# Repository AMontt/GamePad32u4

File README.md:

# GamePad32u4
Basic gamepad using ATMega32u4

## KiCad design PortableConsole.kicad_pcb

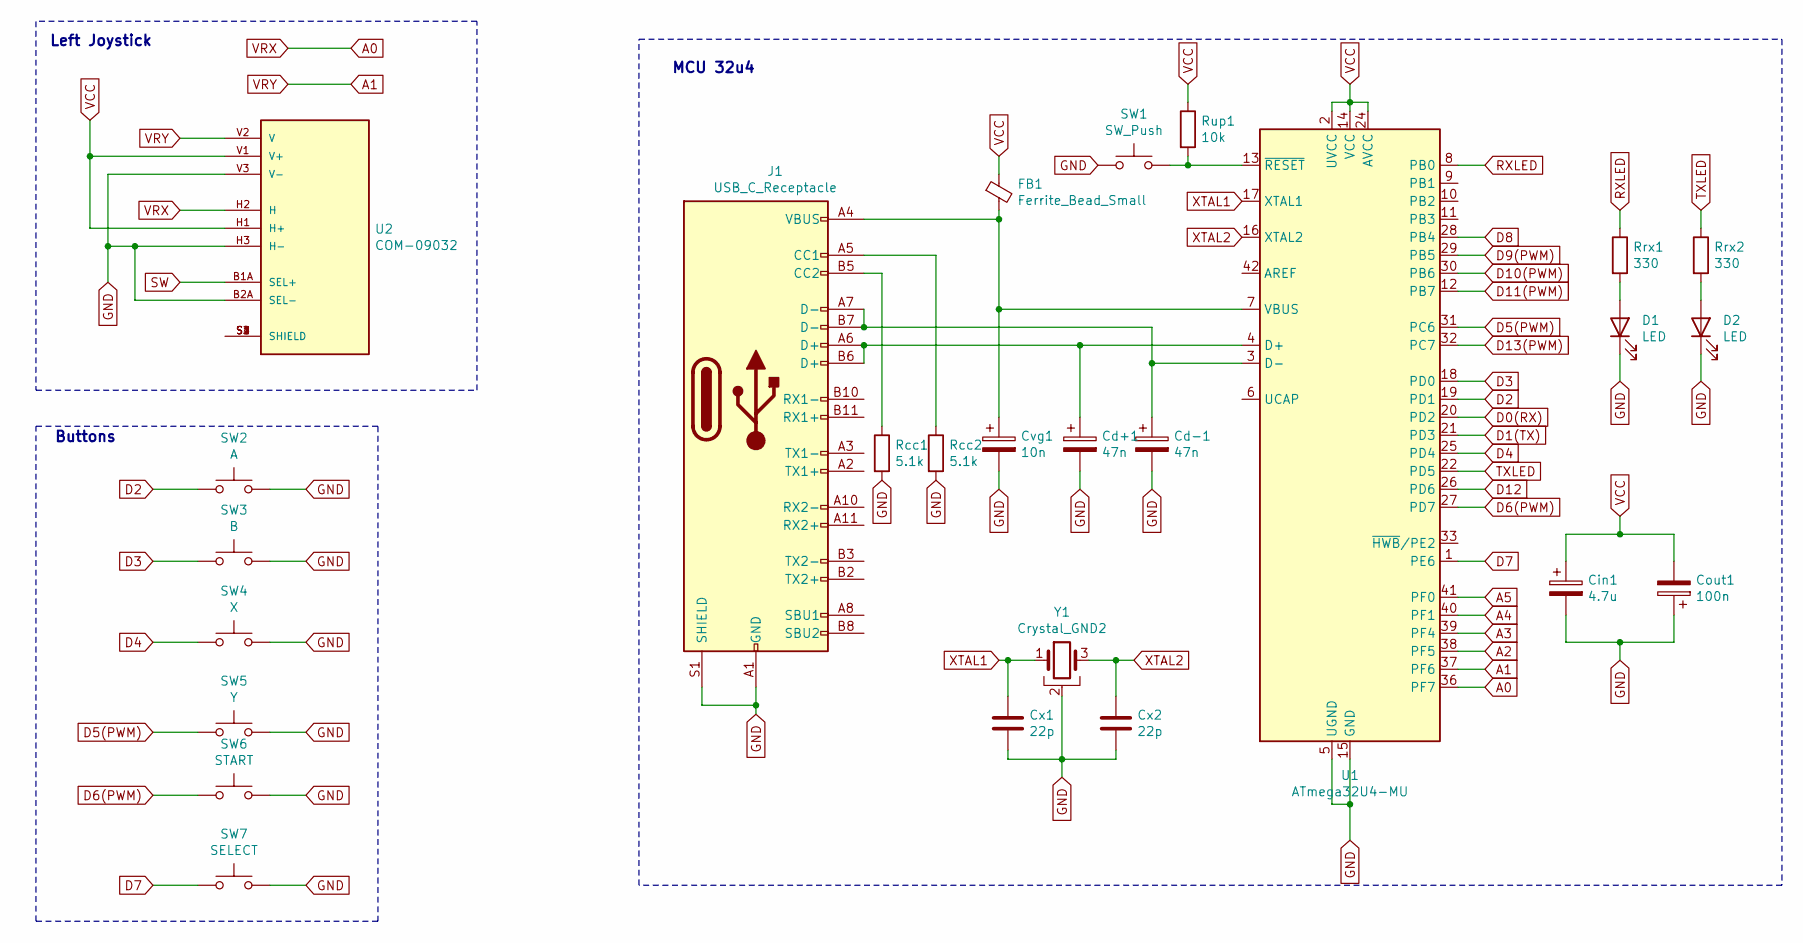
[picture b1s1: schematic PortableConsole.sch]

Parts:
Cd+1: 47n; C_0603_1608Metric
Cd-1: 47n; C_0603_1608Metric
Cin1: 4.7u; C_0603_1608Metric
Cout1: 100n; C_0603_1608Metric_Pad1.08x0.95mm_HandSolder
Cvg1: 10n; C_0402_1005Metric_Pad0.74x0.62mm_HandSolder
Cx1, Cx2: 22p; C_0504_1310Metric_Pad0.83x1.28mm_HandSolder
D1, D2: LED; LED_0402_1005Metric
FB1: Ferrite_Bead_Small; BEADC1608X95N
J1: USB_C_Receptacle; USB_C_Receptacle_Amphenol_12401548E4-2A
Rcc1, Rcc2: 5.1k; R_0402_1005Metric
Rrx1, Rrx2: 330; R_0402_1005Metric
Rup1: 10k; R_0402_1005Metric
SW1: SW_Push; Panasonic_EVQPUM_EVQPUD
SW2: A; SW_SPST_TL3342
SW3: B; SW_SPST_TL3342
SW4: X; SW_SPST_TL3342
SW5: Y; SW_SPST_TL3342
SW6: START; SW_SPST_TL3342
SW7: SELECT; SW_SPST_TL3342
U1: ATmega32U4-MU; QFN-44-1EP_7x7mm_P0.5mm_EP5.2x5.2mm
U2: COM-09032; XDCR_COM-09032; PARTREV N/A
Y1: Crystal_GND2; Resonator_SMD_muRata_CSTxExxV-3Pin_3.0x1.1mm_HandSoldering

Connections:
A0: U1.36 (PF7), U2.H2 (H)
A1: U1.37 (PF6), U2.V2 (V)
A2: U1.38 (PF5)
A3: U1.39 (PF4)
A4: U1.40 (PF1)
A5: U1.41 (PF0)
D0(RX): U1.20 (PD2)
D1(TX): U1.21 (PD3)
D2: SW2.1, U1.19 (PD1)
D3: SW3.1, U1.18 (PD0)
D4: SW4.1, U1.25 (PD4)
D5(PWM): SW5.1, U1.31 (PC6)
D6(PWM): SW6.1, U1.27 (PD7)
D7: SW7.1, U1.1 (PE6)
D8: U1.28 (PB4)
D9(PWM): U1.29 (PB5)
D10(PWM): U1.30 (PB6)
D11(PWM): U1.12 (PB7)
D12: U1.26 (PD6)
D13(PWM): U1.32 (PC7)
GND: Cd+1.2, Cd-1.2, Cin1.2, Cout1.1, Cvg1.2, Cx1.2, Cx2.2, D1.1 (K), D2.1 (K), J1.A1 (GND), J1.A12 (GND), J1.B1 (GND), J1.B12 (GND), J1.S1 (SHIELD), Rcc1.2, Rcc2.2, SW1.1, SW2.2, SW3.2, SW4.2, SW5.2, SW6.2, SW7.2, U1.5 (UGND), U1.15 (GND), U1.23 (GND), U1.35 (GND), U1.43 (GND), U1.45 (GND), U2.B2A (SEL-), U2.H3 (H-), U2.V3 (V-), Y1.2
unnamed: Cd+1.1, J1.A6 (D+), J1.B6 (D+), U1.4 (D+)
unnamed: Cd-1.1, J1.A7 (D-), J1.B7 (D-), U1.3 (D-)
unnamed: Cvg1.1, FB1.2, J1.A4 (VBUS), J1.A9 (VBUS), J1.B4 (VBUS), J1.B9 (VBUS), U1.7 (VBUS)
unnamed: D1.2 (A), Rrx1.2
unnamed: D2.2 (A), Rrx2.2
unnamed: J1.A5 (CC1), Rcc2.1
unnamed: J1.B5 (CC2), Rcc1.1
unnamed: Rup1.2, SW1.2, U1.13 (~RESET)
unnamed: U2.S1 (SHIELD), U2.S2 (SHIELD), U2.S3 (SHIELD), U2.S4 (SHIELD)
RXLED: Rrx1.1, U1.8 (PB0)
SW: U2.B1A (SEL+)
TXLED: Rrx2.1, U1.22 (PD5)
VCC: Cin1.1, Cout1.2, FB1.1, Rup1.1, U1.2 (UVCC), U1.14 (VCC), U1.24 (AVCC), U1.34 (VCC), U1.44 (AVCC), U2.H1 (H+), U2.V1 (V+)
XTAL1: Cx1.1, U1.17 (XTAL1), Y1.1
XTAL2: Cx2.1, U1.16 (XTAL2), Y1.3

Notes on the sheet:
Left Joystick
MCU 32u4
Buttons

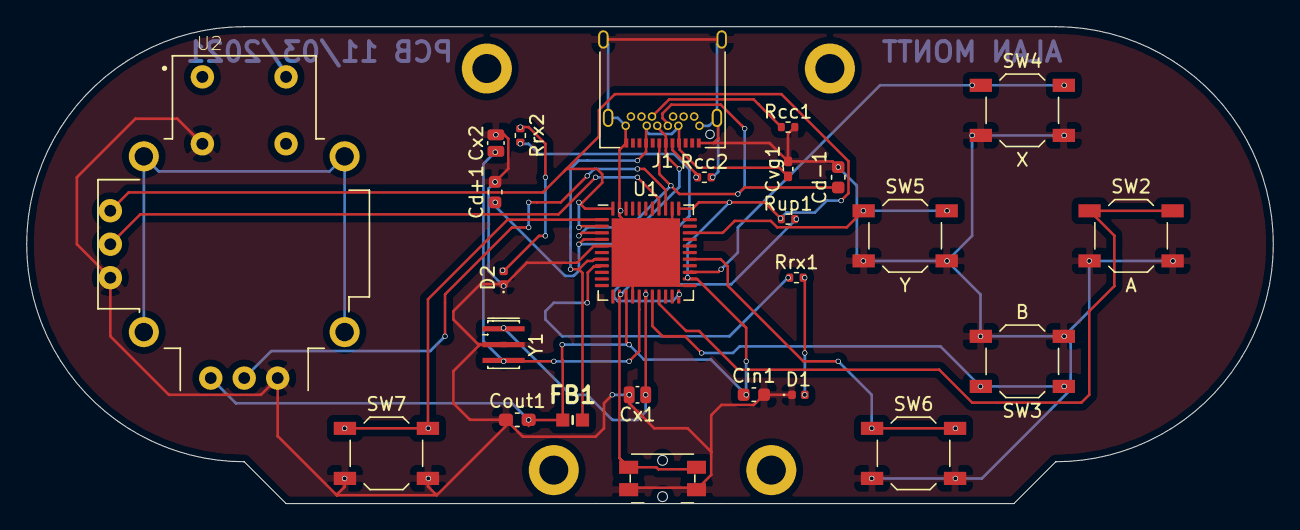
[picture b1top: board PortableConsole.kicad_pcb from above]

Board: 2 copper layers, 94.6 x 36.2 mm, 26 parts (0 on the bottom side), 23 nets.

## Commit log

2021-03-12 Schematic + PCB
    Schematic design for Gamepad
